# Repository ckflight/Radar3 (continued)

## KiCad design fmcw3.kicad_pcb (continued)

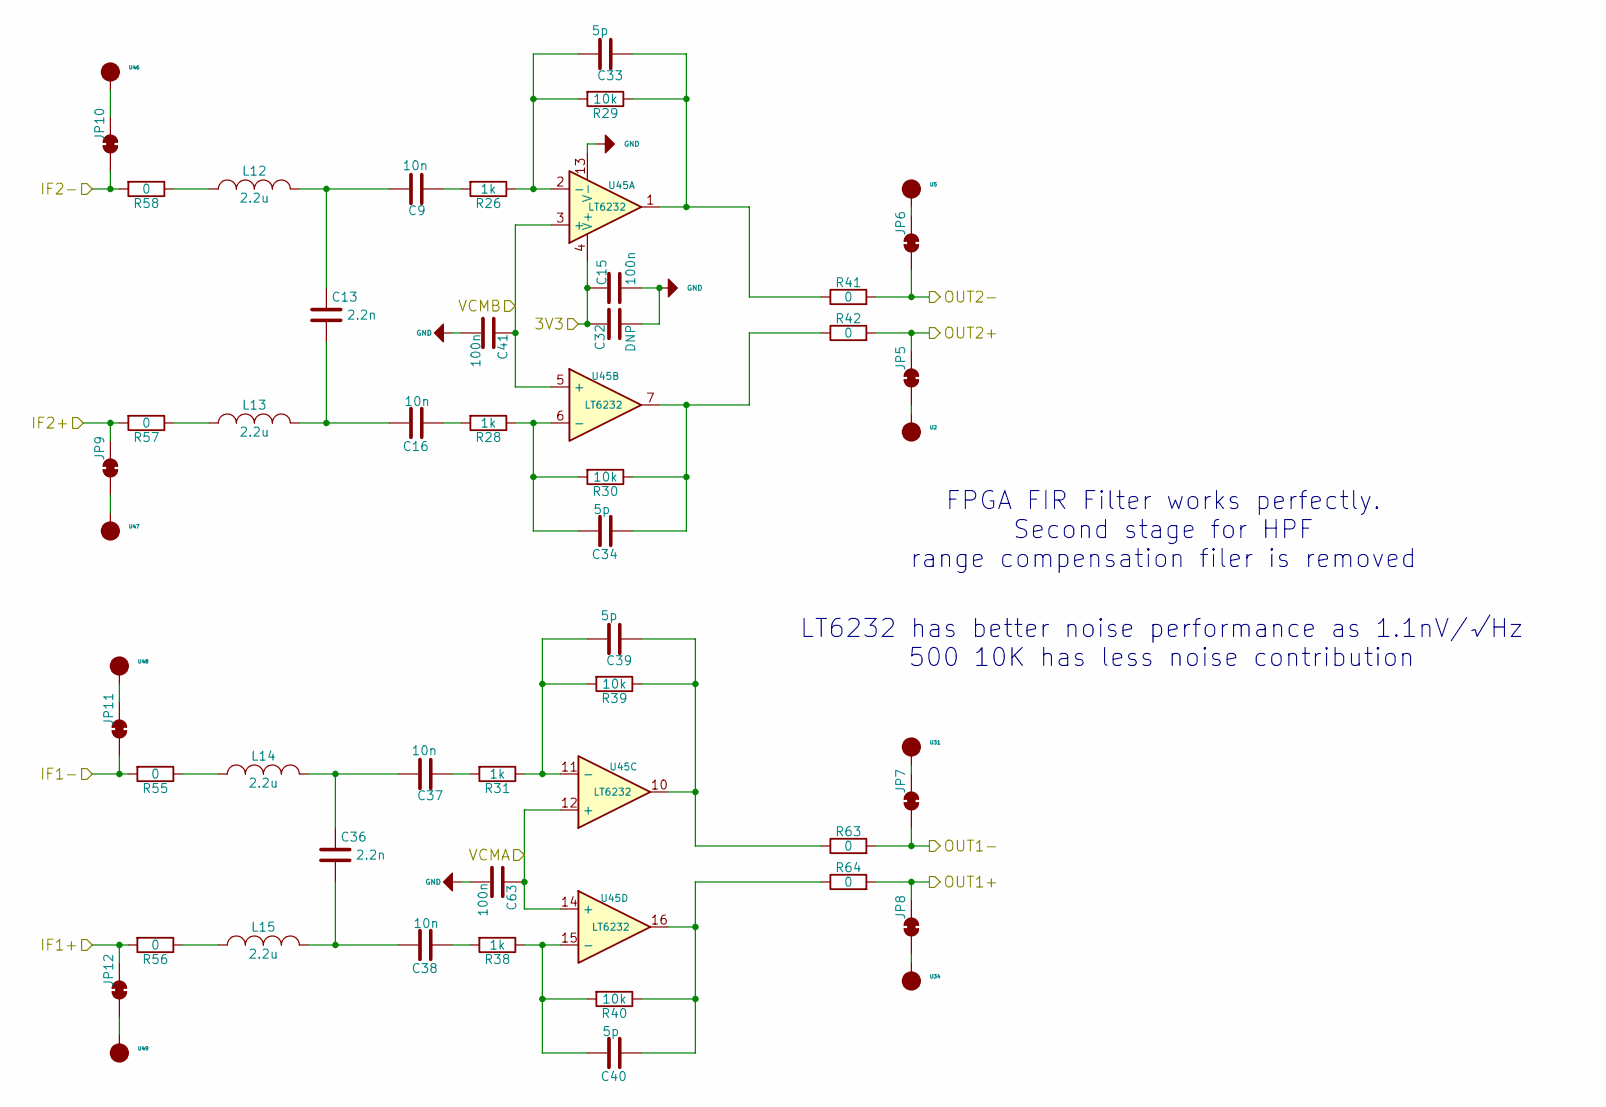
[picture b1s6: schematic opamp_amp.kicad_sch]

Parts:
C9, C16, C37, C38: 10n; SMD_0402
C13, C36: 2.2n; SMD_0402
C15, C41, C63: 100n; SMD_0402
C32: DNP; SMD_0805
C33, C34, C39, C40: 5p; SMD_0402
JP5, JP6, JP7, JP8, JP9, JP10, JP11, JP12: SolderJumper_2_Bridged; SolderPad_2_Bridge
L12, L13, L14, L15: 2.2u; SMD_0805
R26, R28, R31, R38: 1k; SMD_0402
R29, R30, R39, R40: 10k; SMD_0402
R41, R42, R55, R56, R57, R58, R63, R64: 0; SMD_0402
U2, U5, U31, U34, U46, U47, U48, U49: SolderPad_1_Circle; SolderPad_1_1.0mm_SMD_Circle
U45: LT6232; SSOP16_3.9x4.9mm_P0.635mm

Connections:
/3V3A: C15.1, C32.1, U45.4 (V+); also elsewhere on the board
/ADC1+: JP8.2 (B), R64.2; also elsewhere on the board
/ADC1-: JP7.1 (A), R63.2; also elsewhere on the board
/ADC2+: JP5.2 (B), R42.2; also elsewhere on the board
/ADC2-: JP6.1 (A), R41.2; also elsewhere on the board
/ADC_VCMA: C63.1, U45.12 (+), U45.14 (+); also elsewhere on the board
/ADC_VCMB: C41.1, U45.3 (+), U45.5 (+); also elsewhere on the board
/mixer/IF1+: JP12.2 (B), R56.2; also elsewhere on the board
/mixer/IF1-: JP11.1 (A), R55.2; also elsewhere on the board
/mixer/IF2+: JP9.2 (B), R57.2; also elsewhere on the board
/mixer/IF2-: JP10.1 (A), R58.2; also elsewhere on the board
GND: C15.2, C32.2, C41.2, C63.2, U45.13 (V-); also elsewhere on the board
unnamed: C9.1, R26.2
unnamed: C9.2, C13.1, L12.2
unnamed: C13.2, C16.2, L13.2
unnamed: C16.1, R28.2
unnamed: C33.1, R29.1, R41.1, U45.1
unnamed: C34.1, R30.1, R42.1, U45.7
unnamed: C36.1, C37.2, L14.2
unnamed: C36.2, C38.2, L15.2
unnamed: C37.1, R31.2
unnamed: C38.1, R38.2
unnamed: C39.1, R39.1, R63.1, U45.10
unnamed: C40.1, R40.1, R64.1, U45.16
unnamed: JP5.1 (A), U2.1
unnamed: JP6.2 (B), U5.1
unnamed: JP7.2 (B), U31.1
unnamed: JP8.1 (A), U34.1
unnamed: JP9.1 (A), U47.1
unnamed: JP10.2 (B), U46.1
unnamed: JP11.2 (B), U48.1
unnamed: JP12.1 (A), U49.1
unnamed: L12.1, R58.1
unnamed: L13.1, R57.1
unnamed: L14.1, R55.1
unnamed: L15.1, R56.1
unnamed: C33.2, R26.1, R29.2, U45.2 (-)
unnamed: C34.2, R28.1, R30.2, U45.6 (-)
unnamed: C39.2, R31.1, R39.2, U45.11 (-)
unnamed: C40.2, R38.1, R40.2, U45.15 (-)

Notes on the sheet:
LT6232 has better noise performance as 1.1nV/√Hz 500 10K has less noise contribution
FPGA FIR Filter works perfectly. Second stage for HPF range compensation filer is removed

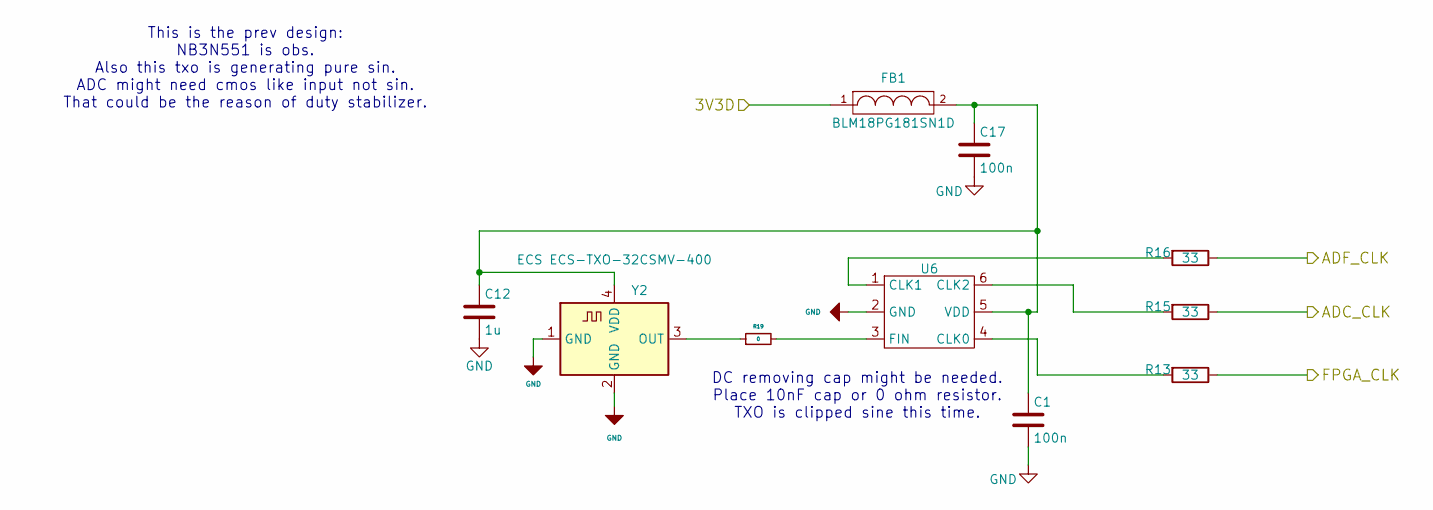
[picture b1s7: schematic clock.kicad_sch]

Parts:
C1, C17: 100n; SMD_0402
C12: 1u; SMD_0603
FB1: BLM18PG181SN1D; SMD_0603
R13, R15, R16: 33; SMD_0402
R19: 0; SMD_0402
U6: PL133-37; SOT23_6
Y2: ECS ECS-TXO-32CSMV-400; Oscillator_SMD_ECS_2520MV-xxx-xx-4Pin_2.5x2.0mm

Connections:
/3V3D: FB1.1; also elsewhere on the board
/ADC_CLK: R15.1; also elsewhere on the board
/ADF_CLK_REF: R16.1; also elsewhere on the board
/FPGA_CLK: R13.1; also elsewhere on the board
GND: C1.2, C12.2, C17.2, U6.2 (GND), Y2.1 (GND), Y2.2 (GND); also elsewhere on the board
unnamed: R13.2, U6.4 (CLK0)
unnamed: R16.2, U6.1 (CLK1)
unnamed: R15.2, U6.6 (CLK2)
unnamed: R19.2, U6.3 (FIN)
unnamed: C1.1, C12.1, C17.1, FB1.2, U6.5 (VDD), Y2.4 (VDD)
unnamed: R19.1, Y2.3 (OUT)

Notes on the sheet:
DC removing cap might be needed. Place 10nF cap or 0 ohm resistor. TXO is clipped sine this time.
This is the prev design: NB3N551 is obs. Also this txo is generating pure sin. ADC might need cmos like input not sin. That could be the reason of duty stabilizer.

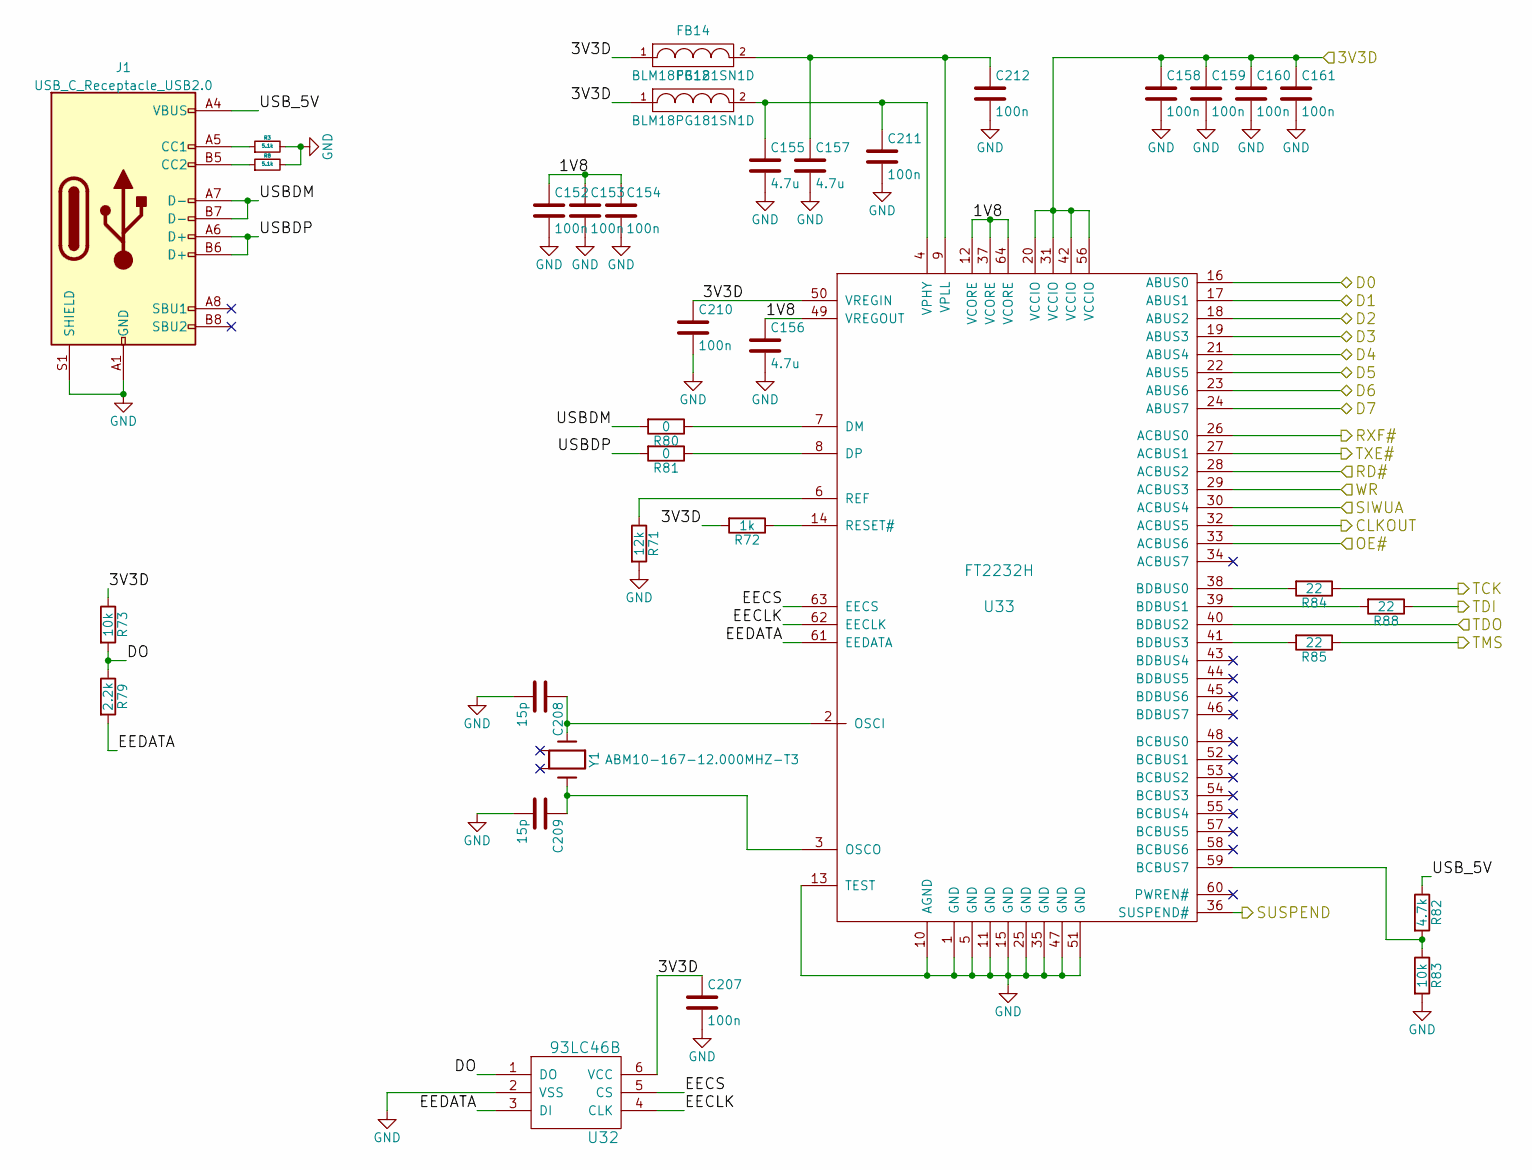
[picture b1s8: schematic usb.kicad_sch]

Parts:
C152, C153, C154, C158, C159, C160, C161, C207, C210, C211, C212: 100n; SMD_0402
C155, C156, C157: 4.7u; SMD_0603
C208, C209: 15p; SMD_0402
FB12, FB14: BLM18PG181SN1D; SMD_0603
J1: USB_C_Receptacle_USB2.0; USB_C_Receptacle_GCT_USB4105-xx-A_16P_TopMnt_Horizontal
R3, R8: 5.1k; SMD_0402
R71: 12k; SMD_0402
R72: 1k; SMD_0402
R73, R83: 10k; SMD_0402
R79: 2.2k; SMD_0402
R80, R81: 0; SMD_0402
R82: 4.7k; SMD_0402
R84, R85, R88: 22; SMD_0402
U32: 93LC46B; SOT-23-6
U33: FT2232H; LQFP-64_10x10mm_Pitch0.5mm
Y1: ABM10-167-12.000MHZ-T3; ABM10

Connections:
/3V3D: C158.1, C159.1, C160.1, C161.1, C207.1, C210.1, FB12.1, FB14.1, R72.2, R73.1, U32.6 (VCC), U33.20 (VCCIO), U33.31 (VCCIO), U33.42 (VCCIO), U33.50 (VREGIN), U33.56 (VCCIO); also elsewhere on the board
/fpga/CLKOUT: U33.32 (ACBUS5); also elsewhere on the board
/fpga/FT_D0: U33.16 (ABUS0); also elsewhere on the board
/fpga/FT_D1: U33.17 (ABUS1); also elsewhere on the board
/fpga/FT_D2: U33.18 (ABUS2); also elsewhere on the board
/fpga/FT_D3: U33.19 (ABUS3); also elsewhere on the board
/fpga/FT_D4: U33.21 (ABUS4); also elsewhere on the board
/fpga/FT_D5: U33.22 (ABUS5); also elsewhere on the board
/fpga/FT_D6: U33.23 (ABUS6); also elsewhere on the board
/fpga/FT_D7: U33.24 (ABUS7); also elsewhere on the board
/fpga/FT_SUSPEND: U33.36 (SUSPEND#); also elsewhere on the board
/fpga/FT_TCK: R84.1; also elsewhere on the board
/fpga/FT_TDI: R88.1; also elsewhere on the board
/fpga/FT_TDO: U33.40 (BDBUS2); also elsewhere on the board
/fpga/FT_TMS: R85.1; also elsewhere on the board
/fpga/OE#: U33.33 (ACBUS6); also elsewhere on the board
/fpga/RD#: U33.28 (ACBUS2); also elsewhere on the board
/fpga/RXF#: U33.26 (ACBUS0); also elsewhere on the board
/fpga/SIWUA: U33.30 (ACBUS4); also elsewhere on the board
/fpga/TXE#: U33.27 (ACBUS1); also elsewhere on the board
/fpga/WR: U33.29 (ACBUS3); also elsewhere on the board
/fpga/usb/1V8: C152.1, C153.1, C154.1, C156.1, U33.12 (VCORE), U33.37 (VCORE), U33.49 (VREGOUT), U33.64 (VCORE)
/fpga/usb/DO: R73.2, R79.1, U32.1 (DO)
/fpga/usb/EECLK: U32.4 (CLK), U33.62 (EECLK)
/fpga/usb/EECS: U32.5 (CS), U33.63 (EECS)
/fpga/usb/EEDATA: R79.2, U32.3 (DI), U33.61 (EEDATA)
/fpga/usb/USBDM: J1.A7 (D-), J1.B7 (D-), R80.2
/fpga/usb/USBDP: J1.A6 (D+), J1.B6 (D+), R81.2
/fpga/usb/USB_5V: J1.A4 (VBUS), J1.A9 (VBUS), J1.B4 (VBUS), J1.B9 (VBUS), R82.1
GND: C152.2, C153.2, C154.2, C155.2, C156.2, C157.2, C158.2, C159.2, C160.2, C161.2, C207.2, C208.2, C209.2, C210.2, C211.2, C212.2, J1.A1 (GND), J1.A12 (GND), J1.B1 (GND), J1.B12 (GND), J1.S1 (SHIELD), R3.2, R8.2, R71.2, R83.2, U32.2 (VSS), U33.1 (GND), U33.5 (GND), U33.10 (AGND), U33.11 (GND), U33.13 (TEST), U33.15 (GND), U33.25 (GND), U33.35 (GND), U33.47 (GND), U33.51 (GND); also elsewhere on the board
unnamed: J1.A5 (CC1), R3.1
unnamed: J1.B5 (CC2), R8.1
unnamed: R82.2, R83.1, U33.59 (BCBUS7)
unnamed: R84.2, U33.38 (BDBUS0)
unnamed: R88.2, U33.39 (BDBUS1)
unnamed: R85.2, U33.41 (BDBUS3)
unnamed: R80.1, U33.7 (DM)
unnamed: R81.1, U33.8 (DP)
unnamed: C208.1, U33.2 (OSCI), Y1.1
unnamed: C209.1, U33.3 (OSCO), Y1.3
unnamed: R71.1, U33.6 (REF)
unnamed: R72.1, U33.14 (RESET#)
unnamed: C155.1, C211.1, FB12.2, U33.4 (VPHY)
unnamed: C157.1, C212.1, FB14.2, U33.9 (VPLL)

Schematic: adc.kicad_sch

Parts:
C19, C20, C217, C218, C222, C249: 1u; SMD_0603
C22, C31, C216, C220: 2.2u; SMD_0603
C23, C24, C25, C27, C30, C219, C221, C223, C224, C225: 100n; SMD_0402
C163, C164, C165, C166, C167, C168: 100p; SMD_0402
C248: 10u; SMD_0805
R20, R93: 0; SMD_0402
R21: 33; SMD_0402
R91: 4.7k; SMD_0402
R92: 10k; SMD_0402
R97, R98, R99, R100: 49.9; SMD_0402
U8: LTC2292; QFN-64-1EP_9x9mm_Pitch0.5mm
U39: LP5907-3.0; SOT-23-5

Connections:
/3V3D: C25.1, C225.1, U8.32 (OVDD), U8.49 (OVDD); also elsewhere on the board
/3V8: C248.1, U39.1 (IN), U39.3 (EN); also elsewhere on the board
/ADC1+: R100.2; also elsewhere on the board
/ADC1-: R98.2; also elsewhere on the board
/ADC2+: R97.2; also elsewhere on the board
/ADC2-: R99.2; also elsewhere on the board
/ADC_CLK: R21.2, U8.8 (CLKA), U8.9 (CLKB); also elsewhere on the board
/ADC_VCMA: C216.1, C219.1, U8.61 (VCMA); also elsewhere on the board
/ADC_VCMB: C30.1, C31.1, U8.20 (VCMB); also elsewhere on the board
/fpga/ADC_OE1: U8.58 (~OEA); also elsewhere on the board
/fpga/ADC_OE2: U8.23 (~OEB); also elsewhere on the board
/fpga/ADC_SHDN1: U8.59 (SHDNA); also elsewhere on the board
/fpga/ADC_SHDN2: U8.22 (SHDNB); also elsewhere on the board
/fpga/D0: U8.43 (DA0); also elsewhere on the board
/fpga/D1: U8.44 (DA1); also elsewhere on the board
/fpga/D2: U8.45 (DA2); also elsewhere on the board
/fpga/D3: U8.46 (DA3); also elsewhere on the board
/fpga/D4: U8.47 (DA4); also elsewhere on the board
/fpga/D5: U8.48 (DA5); also elsewhere on the board
/fpga/D6: U8.51 (DA6); also elsewhere on the board
/fpga/D7: U8.52 (DA7); also elsewhere on the board
/fpga/D8: U8.53 (DA8); also elsewhere on the board
/fpga/D9: U8.54 (DA9); also elsewhere on the board
/fpga/D10: U8.55 (DA10); also elsewhere on the board
/fpga/D11: U8.56 (DA11); also elsewhere on the board
/fpga/OFA: U8.57 (OFA); also elsewhere on the board
/fpga/OFB: U8.40 (OFB); also elsewhere on the board
/fpga/adc/3V0: C24.1, C27.1, C222.1, C223.1, C224.1, C249.1, R20.2, R91.1, R93.2, U8.7 (VDD), U8.10 (VDD), U8.18 (VDD), U8.63 (VDD), U39.5 (OUT)
/fpga/adc/REFHA: C217.1, C220.1, C221.1, U8.3 (REFHA), U8.4 (REFHA)
/fpga/adc/REFHB: C19.1, C22.1, C23.1, U8.11 (REFLB), U8.12 (REFLB)
/fpga/adc/REFLA: C218.1, C220.2, C221.2, U8.5 (REFLA), U8.6 (REFLA)
/fpga/adc/REFLB: C20.1, C22.2, C23.2, U8.13 (REFHB), U8.14 (REFHB)
GND: C19.2, C20.2, C24.2, C25.2, C27.2, C30.2, C31.2, C163.1, C165.2, C166.1, C168.2, C216.2, C217.2, C218.2, C219.2, C222.2, C223.2, C224.2, C225.2, C248.2, C249.2, R92.2, U8.17 (GND), U8.31 (OGND), U8.50 (OGND), U8.64 (GND), U8.65 (PAD), U39.2 (GND); also elsewhere on the board
unnamed: C163.2, C164.1, R97.1, U8.1 (AINA+)
unnamed: C164.2, C165.1, R99.1, U8.2 (AINA-)
unnamed: C167.2, C168.1, R100.1, U8.16 (AINB+)
unnamed: C166.2, C167.1, R98.1, U8.15 (AINB-)
unnamed: R91.2, R92.1, U8.60 (MODE)
unnamed: R21.1, U8.21 (MUX)
unnamed: R93.1, U8.62 (SENSEA)
unnamed: R20.1, U8.19 (SENSEB)

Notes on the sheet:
2/3 VDD clock duty stabilizer 2s complement signed output This helped for better waveform
Important Note: ECS-TXO-3225MV is pure sin. Adc does not like sin i guess. Other ref designed used clipped more square like sin. That is why clock stabilizer is needed.

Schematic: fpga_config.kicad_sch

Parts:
C18, C252: 100n; SMD_0402
C170, C171, C187, C189, C190, C191, C192, C193, C197, C198, C199, C200, C201, C202, C203, C204, C250, C251: 470n; SMD_0402
C181: 100u; SMD_1210
C182, C184, C196: 47u; SMD_1206
C183, C185, C186, C188, C194, C195: 4.7u; SMD_0603
CON1: SD_Card_DM3BT; DM3BT-DSF-PEJS
D6: LED; Diode_0603
J2: Connector_02x08; PinHeader_2x8_P2.5mm
R10: DNP; SMD_0402
R14, R112, R117, R118: 4.7k; SMD_0402
R109: 1k; SMD_0402
R110, R114, R115: 0; SMD_0402
SW1, SW2: B3U-1000P; EVP-AWBA2A
U40: W25Q128JV; DFN-S-8-1EP_6x5mm_Pitch1.27mm

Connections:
/1V0: C181.1, C183.1, C184.1, C186.1, C187.1, C189.1, C191.1, C250.1; also elsewhere on the board
/1V8: C182.1, C185.1, C188.1, C190.1, C192.1, C193.1; also elsewhere on the board
/3V3D: C18.1, C170.1, C171.1, C194.1, C195.1, C196.1, C197.1, C198.1, C199.1, C200.1, C201.1, C202.1, C203.1, C204.1, C251.1, C252.1, CON1.4 (VDD), J2.13, J2.15, R10.2, R14.1, R110.1, R112.1, R117.1, R118.1, U40.3 (~WP(IO2)), U40.7 (~HOLD(IO3)), U40.8 (VCC); also elsewhere on the board
/fpga/CARD_DETECT: CON1.9 (CARD_DETECT1); also elsewhere on the board
/fpga/INIT_B: R117.2; also elsewhere on the board
/fpga/M0: R110.2; also elsewhere on the board
/fpga/M1: R114.1; also elsewhere on the board
/fpga/M2: R10.1, R115.1; also elsewhere on the board
/fpga/PIN1: J2.11; also elsewhere on the board
/fpga/PIN2: J2.10; also elsewhere on the board
/fpga/PIN3: J2.8; also elsewhere on the board
/fpga/PIN4: J2.12; also elsewhere on the board
/fpga/PIN5: J2.9; also elsewhere on the board
/fpga/PIN6: J2.7; also elsewhere on the board
/fpga/PIN7: J2.6; also elsewhere on the board
/fpga/PIN8: J2.4; also elsewhere on the board
/fpga/PIN9: J2.2; also elsewhere on the board
/fpga/PIN10: J2.5; also elsewhere on the board
/fpga/PIN11: J2.3; also elsewhere on the board
/fpga/PIN12: J2.1; also elsewhere on the board
/fpga/PROG_B: R112.2, SW2.1; also elsewhere on the board
/fpga/RESET: R14.2, SW1.1; also elsewhere on the board
/fpga/SD_CLK: CON1.5 (CLK); also elsewhere on the board
/fpga/SD_CMD: CON1.3 (CMD); also elsewhere on the board
/fpga/SD_DAT0: CON1.7 (DAT0); also elsewhere on the board
/fpga/SD_DAT1: CON1.8 (DAT1); also elsewhere on the board
/fpga/SD_DAT2: CON1.1 (DAT2); also elsewhere on the board
/fpga/SD_DAT3: CON1.2 (CD/DAT3); also elsewhere on the board
/fpga/SPI_CLK: U40.6 (CLK); also elsewhere on the board
/fpga/SPI_CS: R118.2, U40.1 (~CS); also elsewhere on the board
/fpga/SPI_MISO: U40.2 (DO(IO1)); also elsewhere on the board
/fpga/SPI_MOSI: U40.5 (DI(IO0)); also elsewhere on the board
/fpga/USER_LED: R109.1; also elsewhere on the board
GND: C18.2, C170.2, C171.2, C181.2, C182.2, C183.2, C184.2, C185.2, C186.2, C187.2, C188.2, C189.2, C190.2, C191.2, C192.2, C193.2, C194.2, C195.2, C196.2, C197.2, C198.2, C199.2, C200.2, C201.2, C202.2, C203.2, C204.2, C250.2, C251.2, C252.2, CON1.6 (VSS), CON1.10 (CARD_DETECT2), CON1.11 (SHELL), D6.1 (K), J2.14, J2.16, R114.2, R115.2, SW1.2, SW2.2, U40.4 (GND), U40.9 (EP); also elsewhere on the board
unnamed: D6.2 (A), R109.2

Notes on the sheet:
VCCBRAM
in SPI Flash mode, JTAG can be used.
VCCINT
32 is not supported by vivado openFPGALoader is needed. 128 is same price supported and more memory is available.
VCCAUX
VCCO_0
Mode M[2:0] Master SPI 001 JTAG 101
VCCO

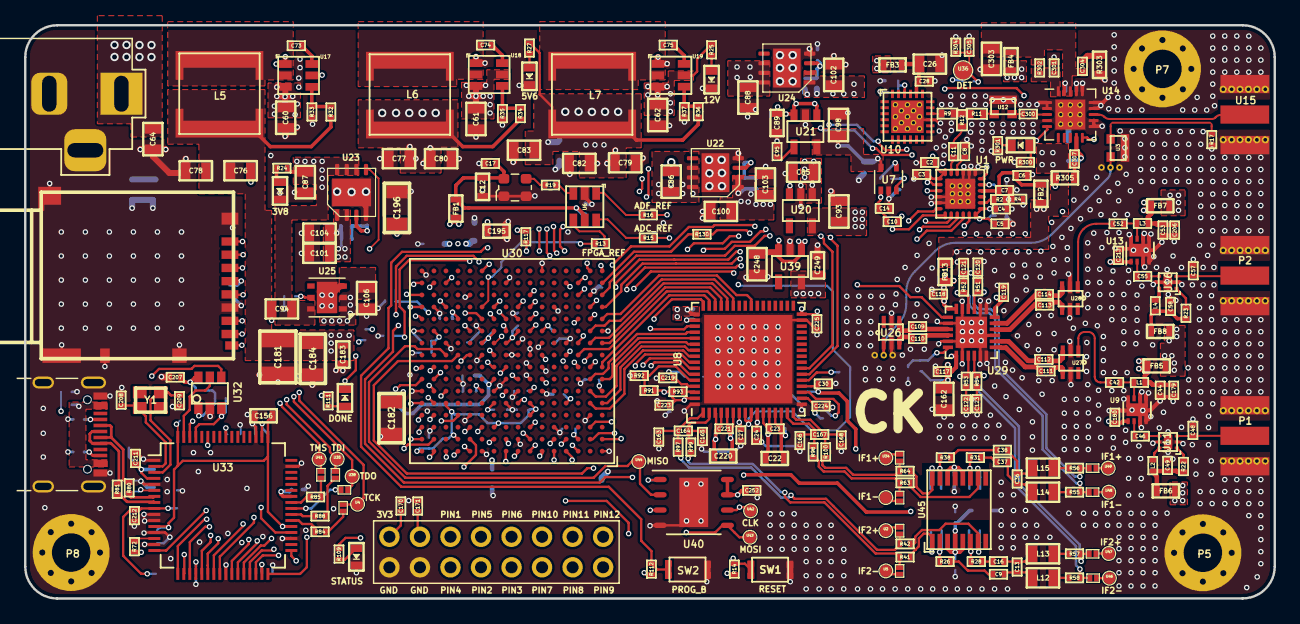
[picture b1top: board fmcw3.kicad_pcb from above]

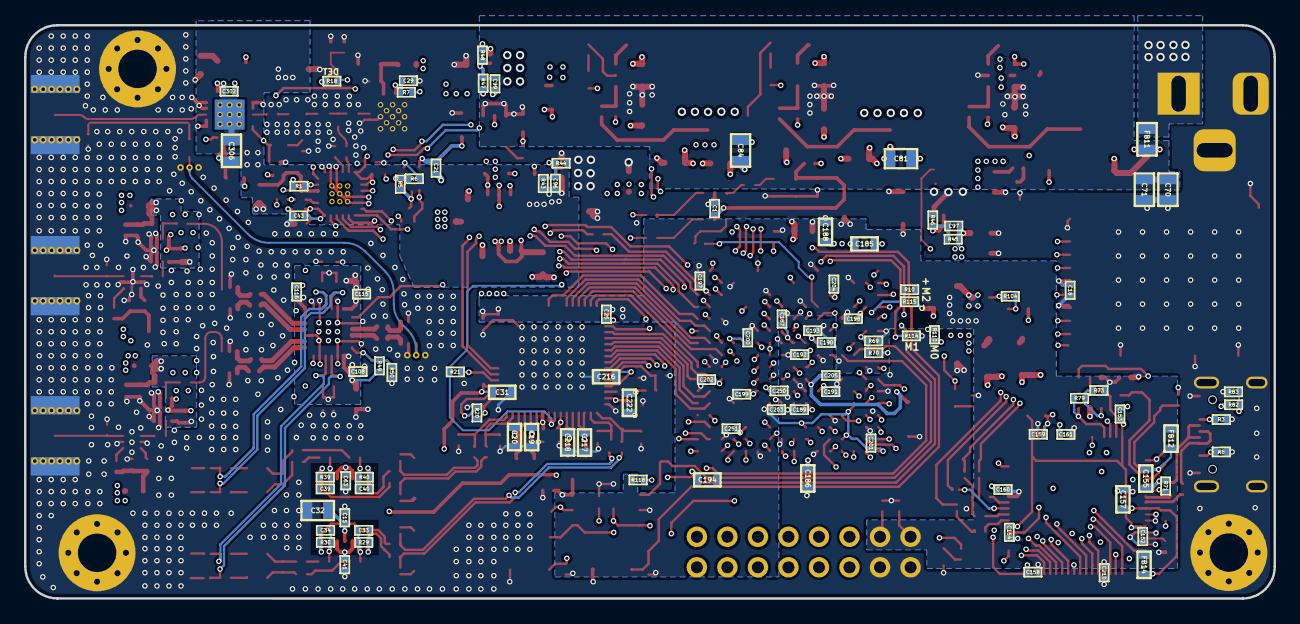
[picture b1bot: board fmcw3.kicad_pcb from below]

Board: 6 copper layers, 104.0 x 47.7 mm, 382 parts (101 on the bottom side), 258 nets.

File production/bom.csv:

Designator,Footprint,Quantity,Value,LCSC Part #
"C1, C108, C115, C116, C120, C121, C122, C123, C15, C152, C153, C154, C158, C159, C160, C161, C17, C18, C2, C207, C21, C210, C211, C212, C219, C221, C223, C224, C225, C23, C24, C25, C252, C27, C30, C301, C302, C4, C41, C43, C49, C58, C6, C63, C73, C74, C75",SMD_0402,47,100n,
"C10, C13, C36",SMD_0402,3,2.2n,
"C100, C101, C102, C106, C162, C248, C26, C303, C306, C60, C61, C62, C64, C70, C71, C76, C77, C78, C79, C80, C81, C82, C83, C84, C85, C86, C87, C88, C93, C94, C98",SMD_0805,31,10u,
"C103, C104, C32",SMD_0805,3,DNP,
"C109, C11, C110, C111, C112, C113, C114, C3, C300, C44, C5, C53, C7, C8",SMD_0402,14,10p,
"C117, C118, C119, C163, C164, C165, C166, C167, C168, C180, C213",SMD_0402,11,100p,
"C12, C19, C20, C217, C218, C222, C249, C89",SMD_0603,8,1u,
"C14, C304, C305, C307",SMD_0402,4,220p,
"C155, C156, C157, C183, C185, C186, C188, C194, C195",SMD_0603,9,4.7u,
"C16, C179, C206, C28, C37, C38, C9, C95",SMD_0402,8,10n,
"C170, C171, C187, C189, C190, C191, C192, C193, C197, C198, C199, C200, C201, C202, C203, C204, C205, C250, C251, C96, C97, C99",SMD_0402,22,470n,
C181,SMD_1210,1,100u,
"C182, C184, C196",SMD_1206,3,47u,
"C208, C209",SMD_0402,2,15p,
"C216, C22, C220, C31",SMD_0603,4,2.2u,
"C29, R10, R50, R69",SMD_0402,4,DNP,
"C33, C34, C39, C40",SMD_0402,4,5p,
"C42, C46, C52, C55",SMD_0402,4,18p,
"C48, C57",SMD_0402,2,0.5p,
CON1,DM3BT-DSF-PEJS,1,SD_Card_DM3BT,
CON2,BarrelJack,1,BARREL_JACK,
"D1, D2, D3, D5, D6, D7",Diode_0603,6,LED,
"F1, F2",RF_via,2,Via,
"FB1, FB12, FB13, FB14, FB2, FB3, FB4, FB5, FB6, FB7, FB8",SMD_0603,11,BLM18PG181SN1D,
FB11,SMD_0805,1,MPZ2012S101AT000,
J1,USB_C_Receptacle_GCT_USB4105-xx-A_16P_TopMnt_Horizontal,1,USB_C_Receptacle_USB2.0,
J2,PinHeader_2x8_P2.5mm,1,Connector_02x08,
"L1, L3",SMD_0402,2,LQW15AN9N9J80D,
"L12, L13, L14, L15",SMD_0805,4,2.2u,
"L2, L4",SMD_0402,2,0.6n,
"L5, L6, L7",SRR6040A,3,33u (SRR6040A-330M),
"P1, P2, U15",CONSMA003.062,3,SMA,
"P5, P7, P8",MountingHole_3.2mm_M3_Pad_Via_mod,3,CONN_01X01,
R1,SMD_0402,1,5.49k,
"R100, R17, R51, R52, R53, R54, R97, R98, R99",SMD_0402,9,49.9,
"R104, R29, R30, R39, R40, R73, R83, R92",SMD_0402,8,10k,
"R109, R111, R24, R25, R27, R300, R301, R4, R72",SMD_0402,9,1k,
"R11, R12, R9",SMD_0402,3,16.9,
"R110, R114, R115, R18, R19, R20, R41, R42, R55, R56, R57, R58, R63, R64, R7, R70, R80, R81, R93",SMD_0402,19,0,
"R112, R117, R118, R14, R5, R6, R82, R91",SMD_0402,8,4.7k,
"R13, R130, R15, R16, R21, R84, R85, R88",SMD_0402,8,33,
"R2, R48",SMD_0402,2,3.3K,
"R22, R23",SMD_0402,2,100,
"R26, R28, R31, R38",SMD_0402,4,500,
"R3, R8",SMD_0402,2,5.1k,
R302,SMD_0402,1,27,
"R303, R305",SMD_0603,2,2,
R304,SMD_0402,1,27.4k,
R32,SMD_0402,1,68k,
"R33, R34, R36",SMD_0402,3,100k,
"R35, R46, R47",SMD_0402,3,18.7K,
"R37, R71",SMD_0402,2,12k,
R43,SMD_0402,1,18k,
"R44, R49",SMD_0402,2,2k,
R45,SMD_0402,1,49.9k,
R79,SMD_0402,1,2.2k,
"SW1, SW2",EVP-AWBA2A,2,B3U-1000P,
U1,VFQFN-24,1,ADF4158,
U10,VQFN-24,1,HMC431LP4,
"U11, U16",XFDFN-6,2,SKY65404,
U12,PAT1220,1,PAT1220-3dB,
"U13, U9",DFN-8-1EP_2x2mm_Pitch0.5mm,2,TRF37A73,
U14,QFN-20-1EP_4x4mm_P0.5mm_EP2.5x2.5mm_ThermalVias,1,TQP5525,
"U17, U18, U19",SOT23_6,3,LMR51420,
"U2, U31, U34, U35, U38, U4, U41, U42, U43, U44, U46, U47, U48, U49, U5",SolderPad_1_1.0mm_SMD_Circle,15,SolderPad_1_Circle,
"U20, U39",SOT-23-5,2,LP5907-3.0,
U21,SOT-23-5,1,LP2985A-10DBVR,
"U22, U23, U24",DFN-8-1EP_4x4mm_P0.8mm_EP2.3x3.24mm,3,LD3920,
U25,DFN-6-1EP_3x3mm_P0.95mm_EP1.7x2.6mm,1,LD3920_33,
"U26, U27, U28",5400BL15B050E,3,5400BL15B0050001E,
U29,QFN-24-1EP_4x4mm_Pitch0.5mm,1,ADL5802,
U3,PAT1220,1,PAT1220-6dB,
U30,FTG256,1,XC7A35T-1FTG256C,
U32,SOT-23-6,1,93LC46B,
U33,LQFP-64_10x10mm_Pitch0.5mm,1,FT2232H,
U36,SolderPad_1_1.5mm_SMD_Circle,1,SolderPad_1_Circle,
U40,DFN-S-8-1EP_6x5mm_Pitch1.27mm,1,W25Q128JV,
U45,SSOP16_3.9x4.9mm_P0.635mm,1,LT6232,
U6,SOT23_6,1,PL133-37,
U7,SOT-353_SC-70-5,1,TLV172DCK,
U8,QFN-64-1EP_9x9mm_Pitch0.5mm,1,LTC2292,
Y1,ABM10,1,ABM10-167-12.000MHZ-T3,
Y2,Oscillator_SMD_ECS_2520MV-xxx-xx-4Pin_2.5x2.0mm,1,ECS ECS-TXO-32CSMV-400,
Z1,Directional_Coupler_15dB_0.169mm_v2,1,15dB COUPLER,

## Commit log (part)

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2025-05-01 Init commit
2025-05-01 Leds are added to schematic netlist is generated will be placed on pcb
2025-08-04 3D models are added. Now done yet
2025-08-12 3 leds are added design is checked. Schematic pin name corrected
2025-08-12 Artix 7 Mode pin 2 was connected to 3.3 and Gnd. It is corrected. It is in JTAG mode for now. I will add dip switch
2025-08-20 Reset button is added. Detout is connected to an adc pin of fpga. Unused pad is deleted. Pins are check. Notes are added on pcb side. No problem related error drc excluded
2025-08-20 DRC rules are checked. Some errors which are not possess any problem excluded
2025-08-20 OSH Park rules version.
2025-08-20 LO trace is soft bended for continuous 50 ohm
2025-08-21 ADC differential length is matched as much as possible for better phase
2025-08-21 ADC path correction
2025-08-21 IF path length matched
2025-08-21 OSH Park version is ready
2025-08-21 CST Studio simulation is made and 50 ohm line is 0.169mm and 0.14mm spacing is required for same 17dB coupling as in oshpark design. Rf traces are corrected with 0.169mm. Directional coupler will be 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
2025-08-22 I have designed 0.17mm directional coupler and placed on pcb. Further improvements for better layout will be done
2025-08-22 0.17mm is correctly simulated on cst studio. It is implemented on pcb
2025-11-01 fpga usb clkout pin and one more pin is changed
2025-11-02 rf path 3h clearance is added. Not finished yet
2025-11-02 rf clearance is done for osh park
2025-11-02 fpga pin change pdf update
2025-12-18 usb rd and clkout pins are routed already. Space to gnd on same layer from rf paths will be added for 50 ohm microstrip line
2025-12-31 rf paths with 2h spacing is added. Differential part after balun will be completed
2025-12-31 balun must be 50:50 since adl5802 inputs are diff 50 ohm. But 0.17 0.17 is making 100 ohm
2026-01-01 0.1 spacing is corrected on board setup and net class rules section. It does not have any error now
2026-01-01 IMPORTANT FIX: ADL5802 if output is 200ohm so diff pull ups must be 100 not 50. I have corrected that
2026-01-01 Important comment is added to the pcb for rf lines. Follow those rules and correct design
2026-01-01 comment is added again
2026-01-02 vias are placed at same rf traces and copper pour areas
2026-01-02 vias are placed
2026-01-04 vias are corrected
2026-01-04 corrected differential rf traces and checked vias. drc has no error
2026-01-04 rf traces vias are completed. It is done. I will do last checks
2026-01-04 pcb design is checked with drc on schematic and pcb. It look good
2026-01-04 Clock buffer path cap changed to resistor.
2026-01-04 Resistor value is changed to 0 ohm
2026-01-04 production files are generated
2026-01-05 production files are generated. Everything is checked.
2026-01-06 after a few minor cap replacement desing is regenerated and sent for production.
2026-03-01 component name correction
2026-05-21 final corrections is done. Working!
2026-05-22 I increased the gap between voltage pours and also corrected signals cutting copper pour. Also not connected gnd occured in some layers are corrected with no copper zoens
2026-05-22 Minor changes are done. Pcb is ready. Production file is added
2026-05-24 clock buffer and txco source is changed. Clock is clipped sin and fanout says cmos square out but it is better anyways. Also traces are 50 ohm as well. Copper pours other minor thinks are changed as 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
2026-05-24 changes are pushed
2026-05-26 final changes
2026-05-26 readme.md file
2026-05-30 hardware changes
2026-05-30 readme.md
2026-05-31 schematic is updated pcb is almost done
2026-05-31 lt6232 implementation is done. Keep out area around opamp will be added
2026-06-02 keepout area is added
2026-06-02 vcom trace width is changed
2026-06-02 checks are done.
2026-06-02 regulator cooper pours are continuous it is checked. gnd vias will be added
2026-06-04 lt6232 is done. I push latest updates
2026-06-04 3.3v regulator is upgraded
2026-06-06 lt6232 is done with vias and copper pours are checked
2026-06-26 DNP components are deleted
2026-06-30 pcb is checked dnp is deleted copper pours are checked
